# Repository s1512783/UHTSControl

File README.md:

# UHTSControl
Control code for UHTS rig (excluding LabView VIs).
Mostly Arduino stuff, some minor changes made to standard libraries.

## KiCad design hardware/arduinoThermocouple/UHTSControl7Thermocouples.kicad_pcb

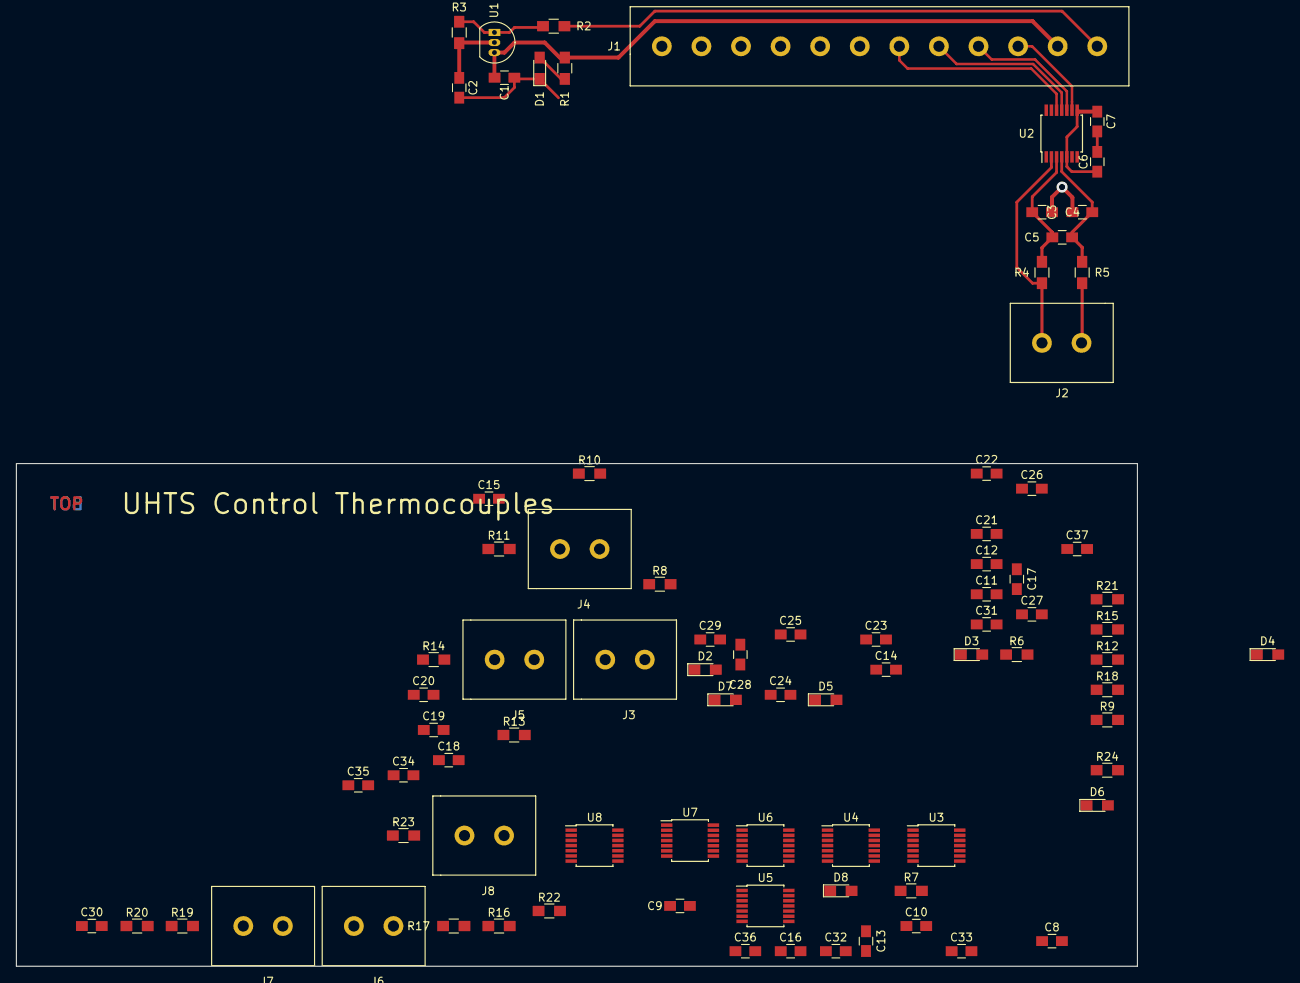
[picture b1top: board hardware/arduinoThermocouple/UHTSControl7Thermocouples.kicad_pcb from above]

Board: 2 copper layers, 141.6 x 63.5 mm, 85 parts (0 on the bottom side), 46 nets.

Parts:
C1: 0.1uF; C_0805_HandSoldering
C2: 1uF; C_0805_HandSoldering
C3, C4, C8, C9, C13, C14, C18, C19, C23, C24, C28, C29, C33, C34: 0.01u; C_0805_HandSoldering
C5, C6, C7, C10, C11, C12, C15, C16, C17, C20, C21, C22, C25, C26, C27, C30, C31, C32, C35, C36, C37: 0.1u; C_0805_HandSoldering
D1, D2, D3, D4, D5, D6, D7, D8: LED; LED_0805_HandSoldering
J1: Conn_01x12; RSPro12-wayScrewTerminalPCBMount
J2, J3, J4, J5, J6, J7, J8: Conn_01x02; RSPro2-wayScrewTerminalPCBMount
R1: 820; R_0805_HandSoldering
R2: 560; R_0805_HandSoldering
R3: 330; R_0805_HandSoldering
R4, R5, R6, R7, R8, R9, R10, R11, R12, R13, R14, R15, R16, R17, R19, R20, R22, R23: 100; R_0805_HandSoldering
R18, R21, R24: R; R_0805_HandSoldering
U1: LM317L_TO92; TO-92_Inline_Narrow_Oval
U2, U3, U4, U5, U6, U7, U8: MAX31856MUD+; TSSOP-14_4.4x5mm_Pitch0.65mm

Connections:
+3V3: C2.1, C6.1, C7.1, C11.1, C12.1, C16.1, C17.1, C21.1, C22.1, C26.1, C27.1, C31.1, C32.1, C36.1, C37.1, R3.1, U1.2, U2.5, U2.8, U3.5, U3.8, U4.5, U4.8, U5.5, U5.8, U6.5, U6.8, U7.5, U7.8, U8.5, U8.8
+VSW: C1.1, J1.2, R1.1, U1.3
/CS0: J1.3, U2.9
/CS1: J1.7, U3.9
/CS2: J1.8, U4.9
/CS3: J1.9, U8.9
/CS4: J1.10, U5.9
/CS5: J1.11, U6.9
/CS6: J1.12, U7.9
/SCK: J1.4, U2.10, U3.10, U4.10, U5.10, U6.10, U7.10, U8.10
/SDI: J1.6, U2.12, U3.12, U4.12, U5.12, U6.12, U7.12, U8.12
/SDO: J1.5, U2.11, U3.11, U4.11, U5.11, U6.11, U7.11, U8.11
GND: C1.2, C2.2, C3.2, C4.2, C6.2, C7.2, C8.2, C9.2, C11.2, C12.2, C13.2, C14.2, C16.2, C17.2, C18.2, C19.2, C21.2, C22.2, C23.2, C24.2, C26.2, C27.2, C28.2, C29.2, C31.2, C32.2, C33.2, C34.2, C36.2, C37.2, D1.1, J1.1, R2.2, R18.1, R21.1, R24.1, U2.1, U2.14, U3.1, U3.14, U4.1, U4.14, U5.1, U5.14, U6.1, U6.14, U7.1, U7.14, U8.1, U8.14
unnamed: C3.1, C5.2, R5.1, U2.4
unnamed: C4.1, C5.1, R4.1, U2.3
unnamed: C9.1, C10.1, R6.1, U3.3
unnamed: C8.1, C10.2, R7.1, U3.4
unnamed: C13.1, C15.2, R9.1, U4.4
unnamed: C14.1, C15.1, R8.1, U4.3
unnamed: C18.1, C20.2, R11.1, U5.4
unnamed: C19.1, C20.1, R10.1, U5.3
unnamed: C23.1, C25.2, R13.1, U6.4
unnamed: C24.1, C25.1, R12.1, U6.3
unnamed: C28.1, C30.2, R15.1, R20.1, U7.4
unnamed: C29.1, C30.1, R14.1, R19.1, U7.3
unnamed: C33.1, C35.2, R17.1, R23.1, U8.4
unnamed: C34.1, C35.1, R16.1, R22.1, U8.3
unnamed: D1.2, R1.2
unnamed: D6.1, R18.2
unnamed: D7.1, R21.2
unnamed: D8.1, R24.2
unnamed: J2.1, R5.2
unnamed: J2.2, R4.2, U2.2
unnamed: J3.1, R7.2
unnamed: J3.2, R6.2, U3.2
unnamed: J4.1, R9.2
unnamed: J4.2, R8.2, U4.2
unnamed: J5.1, R11.2
unnamed: J5.2, R10.2, U5.2
unnamed: J6.1, R13.2
unnamed: J6.2, R12.2, U6.2
unnamed: J7.1, R15.2, R20.2
unnamed: J7.2, R14.2, R19.2, U7.2
unnamed: J8.1, R17.2, R23.2
unnamed: J8.2, R16.2, R22.2, U8.2
unnamed: R2.1, R3.2, U1.1

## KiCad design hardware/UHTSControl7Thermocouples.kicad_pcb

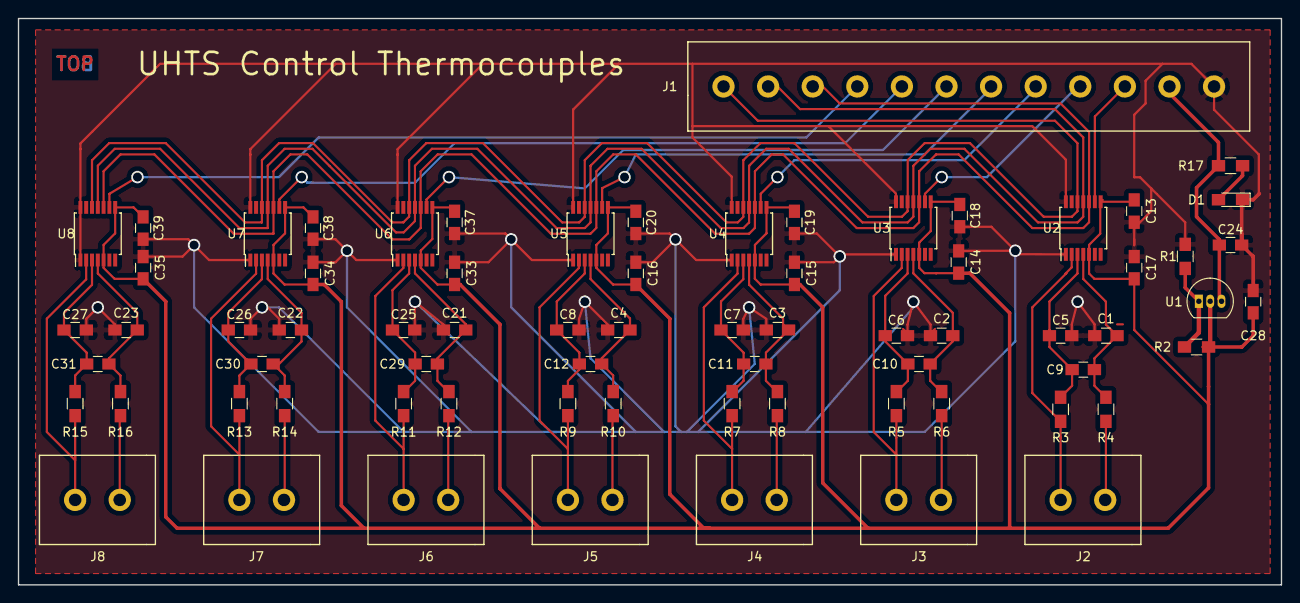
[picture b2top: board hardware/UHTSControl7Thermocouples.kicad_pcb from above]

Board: 2 copper layers, 141.6 x 63.5 mm, 71 parts (0 on the bottom side), 43 nets.

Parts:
C1, C2, C3, C4, C5, C6, C7, C8, C21, C22, C23, C25, C26, C27: 0.01u; C_0805_HandSoldering
C9, C10, C11, C12, C13, C14, C15, C16, C17, C18, C19, C20, C29, C30, C31, C33, C34, C35, C37, C38, C39: 0.1u; C_0805_HandSoldering
C24: 0.1uF; C_0805_HandSoldering
C28: 1uF; C_0805_HandSoldering
D1: LED; LED_0805_HandSoldering
J1: Conn_01x12; RSPro12-wayScrewTerminalPCBMount
J2, J3, J4, J5, J6, J7, J8: Conn_01x02; RSPro2-wayScrewTerminalPCBMount
R1: 560; R_0805_HandSoldering
R2: 330; R_0805_HandSoldering
R3, R4, R5, R6, R7, R8, R9, R10, R11, R12, R13, R14, R15, R16: 100; R_0805_HandSoldering
R17: 820; R_0805_HandSoldering
U1: LM317L_TO92; TO-92_Inline_Narrow_Oval
U2, U3, U4, U5, U6, U7, U8: MAX31856MUD+; TSSOP-14_4.4x5mm_Pitch0.65mm

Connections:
+3V3: C13.1, C14.1, C15.1, C16.1, C17.1, C18.1, C19.1, C20.1, C28.1, C33.1, C34.1, C35.1, C37.1, C38.1, C39.1, R2.1, U1.2, U2.5, U2.8, U3.5, U3.8, U4.5, U4.8, U5.5, U5.8, U6.5, U6.8, U7.5, U7.8, U8.5, U8.8
+VSW: C24.1, J1.2, R17.1, U1.3
/CS0: J1.3, U2.9
/CS1: J1.4, U3.9
/CS2: J1.5, U4.9
/CS3: J1.6, U5.9
/CS4: J1.7, U6.9
/CS5: J1.8, U7.9
/CS6: J1.9, U8.9
/SCK: J1.10, U2.10, U3.10, U4.10, U5.10, U6.10, U7.10, U8.10
/SDI: J1.12, U2.12, U3.12, U4.12, U5.12, U6.12, U7.12, U8.12
/SDO: J1.11, U2.11, U3.11, U4.11, U5.11, U6.11, U7.11, U8.11
GND: C1.2, C2.2, C3.2, C4.2, C5.2, C6.2, C7.2, C8.2, C13.2, C14.2, C15.2, C16.2, C17.2, C18.2, C19.2, C20.2, C21.2, C22.2, C23.2, C24.2, C25.2, C26.2, C27.2, C28.2, C33.2, C34.2, C35.2, C37.2, C38.2, C39.2, D1.1, J1.1, R1.2, U2.1, U2.14, U3.1, U3.14, U4.1, U4.14, U5.1, U5.14, U6.1, U6.14, U7.1, U7.14, U8.1, U8.14
unnamed: C1.1, C9.2, R4.1, U2.4
unnamed: C5.1, C9.1, R3.1, U2.3
unnamed: C6.1, C10.1, R5.1, U3.3
unnamed: C2.1, C10.2, R6.1, U3.4
unnamed: C7.1, C11.1, R7.1, U4.3
unnamed: C3.1, C11.2, R8.1, U4.4
unnamed: C8.1, C12.1, R9.1, U5.3
unnamed: C4.1, C12.2, R10.1, U5.4
unnamed: C21.1, C29.2, R12.1, U6.4
unnamed: C22.1, C30.2, R14.1, U7.4
unnamed: C23.1, C31.2, R16.1, U8.4
unnamed: C25.1, C29.1, R11.1, U6.3
unnamed: C26.1, C30.1, R13.1, U7.3
unnamed: C27.1, C31.1, R15.1, U8.3
unnamed: D1.2, R17.2
unnamed: J2.1, R4.2
unnamed: J2.2, R3.2, U2.2
unnamed: J3.1, R6.2
unnamed: J3.2, R5.2, U3.2
unnamed: J4.1, R8.2
unnamed: J4.2, R7.2, U4.2
unnamed: J5.1, R10.2
unnamed: J5.2, R9.2, U5.2
unnamed: J6.1, R12.2
unnamed: J6.2, R11.2, U6.2
unnamed: J7.1, R14.2
unnamed: J7.2, R13.2, U7.2
unnamed: J8.1, R16.2
unnamed: J8.2, R15.2, U8.2
unnamed: R1.1, R2.2, U1.1

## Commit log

2018-01-19 Learning github
    By updating README
2018-01-19 Arduino code
2018-01-19 Create note
2018-01-19 Rename UHTSControl.ino to Arduino/UHTSControl.ino
2018-01-19 Rename modbusMap.txt to Arduino/modbusMap.txt
2018-01-19 Create library
2018-01-19 Adding thermocouple libraries
    Adafruit libraries with functions to give temperatures in Kelvin
2018-02-08 Create arduinoThermocoupleBoard
2018-02-08 1st attempt at KiCad
2018-02-08 Trying to use git with KiCad
2018-02-10 Trying to learn python scripting in KiCad.
2018-02-11 Trying to use KiCad with python, doesn't work on Fedora though
